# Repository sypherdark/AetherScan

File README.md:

# AetherScan — Autonomous Indoor 3D Scanning Drone

<p align="center">
  <strong>A drone that flies itself through an unknown indoor space, maps it in real time, and exports a 3D reconstruction.</strong>
</p>

AetherScan is a from-scratch indoor drone **autonomy stack** — 6-DoF physics, SLAM,
frontier + coverage exploration, and semantic 3D reconstruction — built to the point
where it demonstrates **coverage parity flying on its own drifting pose estimate vs.
flying on ground truth**, in simulation. The remaining gaps to real hardware are
identified, measured, and tracked in [ROADMAP.md](ROADMAP.md) and
[REALWORLD_READINESS.md](REALWORLD_READINESS.md).

> **What actually runs:** the `redwood_sim/` Python backend (all physics, sensing,
> mapping, planning) streaming state over a WebSocket to a Next.js + React Three Fiber
> dashboard. **You do not need ROS 2 or Gazebo to run AetherScan.** The
> `aetherscan_ws/` ROS 2 workspace is scaffolding for the eventual hardware-transfer
> target — see [Repository layout](#repository-layout).

---

## How it works

Two independent processes with a single clean data contract between them.

```
┌──────────────────────────── redwood_sim/ (Python) ────────────────────────────┐
│                          ALL computation lives here                            │
│                                                                                │
│   physics.py ──► controls.py ──► navigation.py ──► discovery_map.py            │
│   (RK4 6-DoF      (cascaded      (frontier +        (log-odds occupancy        │
│    @ 500 Hz)       PID)           coverage A*)       grid, 0.2 m)              │
│        │              │               │                   │                    │
│   sensors.py    state_estimation.py   scan_matching.py    exporters.py         │
│   (168-ray       (drifting pose       (Olson 2009         (PLY / GLB / SVG     │
│    LiDAR sim)     estimate)            SLAM correction)     deliverables)       │
│                                                                                │
│                     bridge/server.py  ──►  WebSocket :8765  (20 Hz state)      │
└────────────────────────────────────────────────────────────────────────────────┘
                                      │
                          JSON over WebSocket
                                      │
┌──────────────────────── dashboard/ (Next.js + R3F) ───────────────────────────┐
│                       DISPLAY ONLY — zero physics, zero planning               │
│                                                                                │
│   ScanEnvironment   PointCloudRenderer   DiscoveredMap   PathVisualization     │
│   (loads scene GLB) (streams recon cloud)(occupancy grid)(planned path)        │
│                          MissionControl (start / stop / god-mode)              │
└────────────────────────────────────────────────────────────────────────────────┘
```

**Invariant #0:** the dashboard never computes physics or planning. It is a terminal.
Every number it draws was produced in Python and shipped over the socket.

A single mission loop: the drone starts with an **empty** map (everything unknown).
Each tick it raycasts a 168-ray LiDAR against the scene, folds the hits into a
log-odds occupancy grid, picks the next frontier (using a FUEL-style global tour to
avoid re-walking corridors), plans an obstacle-inflated A* path to it, and flies there
under a cascaded PID controller — while a correlative scan-matcher bounds the drift in
its self-estimated pose. Scanned points accumulate into a voxel-deduplicated cloud you
can export as a colored PLY, a Poisson GLB mesh, and an SVG floor plan.

---

## Quick start (no ROS, no Docker, no GPU)

Requires **Python 3.11+** (Apple Silicon: install via Homebrew — the system 3.9
segfaults on the Open3D BVH build) and **Node 18+**.

### 1. Set up the physics backend
```bash
cd redwood_sim
./setup-macos.sh        # creates .venv (Python 3.11) and installs requirements.txt
#  …or manually:
#  python3.11 -m venv .venv && .venv/bin/pip install -r requirements.txt
```

### 2. Run the two processes

**One-shot convenience script** (starts the bridge headless, then the dashboard):
```bash
./run-aetherscan.sh --dashboard            # from repo root
./run-aetherscan.sh --dashboard --scene room_0    # pick a scene
# → http://localhost:3000
```

**Or run them by hand in two terminals:**
```bash
# Terminal 1 — physics bridge (WebSocket ws://127.0.0.1:8765)
cd redwood_sim
.venv/bin/python -m bridge --scene apartment_1

# Terminal 2 — dashboard
cd dashboard
npm install
npm run dev
# → http://localhost:3000
```

Open `http://localhost:3000`, pick a scene, hit **Start Mission**, and watch the drone
explore. The fuchsia **GOD** button enables ~3× time acceleration.

> **Note on scene meshes:** the dashboard's visual `.glb` meshes and the backend's
> collision meshes are **not** in the repo (they're hundreds of MB, generated from the
> Meta Replica dataset). The physics bridge runs fine without them; the 3D viewport
> will be empty until you generate the assets — see [Scene assets](#scene-assets).

### 3. Run the tests
```bash
cd redwood_sim
.venv/bin/python -m pytest tests -q        # 8 state-estimation regression tests
```

---

## The WebSocket protocol

The bridge speaks JSON over `ws://127.0.0.1:8765`, broadcasting state at 20 Hz.

| Message | Direction | Payload |
|---|---|---|
| `hello` | server→client | `visual_mesh_url`, `scene_bounds` (ROS ENU frame, never pre-transformed) |
| `scene_changed` | server→client | same as `hello`, on scene switch |
| `state` (20 Hz) | server→client | `position`, `quaternion`, `velocity`, `tilt`, `altitude`, `coverage_pct`, `total_points`, `path`, `discovery_map`, `map_points` (new points since last frame), `localization{ mode, pos_drift_m, yaw_drift_deg, slam_corrections, slam_match_score, slam_health }`, `god_mode` |
| `set_scene` | client→server | switch the active scene |
| `set_god_mode` | client→server | toggle 3× time acceleration |
| `export_scan` | client→server | run the PLY/GLB/SVG export pipeline async; replies `export_started` / `export_complete{ urls, files, errors }` |

Reconstruction points are streamed as **deltas** (`map_points` = new-since-last-frame),
and the frontend uploads only new points into a preallocated 500k buffer — it never
rebuilds the cloud. All server sends pass through a single `asyncio.Lock` so a
scene-switch can't race the 20 Hz broadcast and drop the connection.

**Coordinate convention:** everything in Python is **Z-up ROS / ENU** (X=forward,
Y=left, Z=up). The Three.js layer applies `rosToThree(x,y,z) = [x, z, -y]` exactly
once, at the scene group. `scene_bounds` cross the wire in the ROS frame, untouched.

Bridge CLI: `python -m bridge --scene <id> [--host 127.0.0.1] [--port 8765] [--rate 20] [--voxel 0.03] [--dt 0.002]`

---

## What's in the autonomy stack

| Module | What it does | Notable detail |
|---|---|---|
| `core/physics.py` | 6-DoF quadrotor rigid body, **RK4 @ 500 Hz** | ~1.45 kg frame, drag, ground effect, Dryden wind; collision resolved per micro-step to prevent tunneling |
| `core/controls.py` | Cascaded PID: position→velocity→attitude→thrust | Correct ZYX-Euler world→body tilt mapping (a swapped-axis bug previously made it fly perpendicular to its command) |
| `core/sensors.py` | 168-ray LiDAR (7 rings × 24), range/normal noise | Configurable FOV (360° RPLIDAR baseline; 87° = D435 camera-class) |
| `core/discovery_map.py` | Log-odds occupancy grid, 0.2 m | Floor hits are FREE at flight altitude; noisy returns can't flip a cell; compact body model fits 0.8 m doorways |
| `core/navigation.py` | Frontier + coverage exploration, A* path-following | FUEL-style global tour ordering: **+15–56 % coverage per meter** |
| `core/state_estimation.py` | Drifting, noisy pose estimate (the sim-to-real seam) | `config.use_estimated_pose` — off for the clean demo |
| `core/scan_matching.py` | Correlative scan-matcher (Olson 2009) + keyframe SLAM | Bounds drift to **0.04–0.10 m** vs. **0.14→0.33 m** unbounded |
| `core/exporters.py` | PLY (semantic-colored) / GLB (Poisson) / SVG floor plan | Written to `dashboard/public/exports/` |

**Headline result:** with `use_estimated_pose=True`, the drone flies entirely on its
own estimate — discovery map, frontier goals, path-following, and trajectory setpoints
all live in the estimated frame — and reaches **coverage parity with ground-truth
navigation** (apartment_1 35.2 % vs 37.0 %; room_0 89.8 % vs 87.2 %), with *lower* tilt
and *fewer* wall contacts. Full audit: [REALWORLD_READINESS.md](REALWORLD_READINESS.md).

---

## Hardware — the physical drone

The simulation defines a real aircraft, and [`hardware/`](hardware/) designs it to
match — **kept in accordance with the software by a checker** that fails if the CAD
ever drifts from the physics model (`hardware/cad/check_against_software.py`).

- **Airframe** — a 360 mm quad-X (1.45 kg, RPLIDAR A2 + RealSense D435i + Jetson
  Orin Nano + Pixhawk/PX4), modelled parametrically in code with
  [build123d](https://github.com/gumyr/build123d). See
  [hardware/cad/](hardware/cad/).
- **Design reviews** — converged through structured multidisciplinary design
  reviews (aerodynamics, mechanical, electrical, software, systems) to a
  **deployment-ready** sign-off, with the sim's inertia reconciled to the
  buildable airframe and the controller re-validated. See
  [hardware/design/](hardware/design/).
- **Electrical** — the Power & Sensor Distribution Board is **defined in code**
  ([atopile](https://github.com/atopile/atopile)) and laid out / 3D-rendered /
  Gerber-exported with **KiCad**. See [hardware/electrical/](hardware/electrical/).
- **Build plan** — funding-staged H0→H4 roadmap; design complete, parts not yet
  bought. [hardware/ROADMAP_HARDWARE.md](hardware/ROADMAP_HARDWARE.md).

A 2-page **investor brief** built from real captured system output lives in
[presentation/](presentation/).

---

## Scene assets

AetherScan ships with **18 Meta Replica scenes** (`apartment_0–2`, `frl_apartment_0–5`,
`office_0–4`, `room_0–2`). For licensing and size reasons the dataset and generated
meshes are **not** committed. To populate the 3D viewport:

1. Obtain the [Replica dataset](https://github.com/facebookresearch/Replica-Dataset)
   and place/symlink scenes under `redwood_sim/data/replica/<id>/`.
2. Generate dashboard visual meshes and backend collision meshes:
   ```bash
   python3 scripts/convert_replica_to_glb.py          # → dashboard/public/meshes/<id>.glb
   python3 scripts/build_collision_meshes_fast.py     # → <id>_collision.ply (~120k tris)
   ```

The physics bridge runs without these (it falls back to built-in/procedural geometry);
they only affect what the dashboard *renders* and what the backend raycasts against.

---

## Repository layout

```
redwood_sim/          ← THE WORKING SYSTEM (Python: physics, sensing, mapping, planning, SLAM)
  core/               ← physics, controls, sensors, discovery_map, navigation, state_estimation, scan_matching, exporters
  bridge/server.py    ← WebSocket bridge :8765
  simulation/engine.py← fixed-timestep mission loop
  tests/              ← state-estimation regression suite
dashboard/            ← Next.js + React Three Fiber UI (display only)
  src/components/three/  ← scene, point cloud, occupancy, path, drone renderers
  src/lib/            ← WebSocket client, scene registry, ROS↔Three transforms
scripts/              ← Replica → GLB conversion, collision-mesh builder, semantics
hardware/             ← THE PHYSICAL DRONE (design, CAD, electrical) — see below
  design/             ← multidisciplinary design reviews & converged spec
  cad/                ← parametric airframe (build123d) + software-accordance checker
  electrical/pcb/     ← code-defined PCB (atopile) + KiCad layout/render/gerbers
  specs/ · bom/       ← system spec, mass/power/inertia budgets, real-parts BOM
presentation/         ← 2-page investor brief (PDF) built from real system output
aetherscan_ws/        ← ROS 2 (Humble) workspace — HARDWARE-TRANSFER TARGET, not required to run the sim
docker/               ← optional containerized sim + dashboard
```

### About the ROS 2 workspace
`aetherscan_ws/` contains a full ROS 2 package set (`description`, `gazebo`,
`navigation`, `perception`, `slam`, `control`, `mission`, `bringup`). It is the
**intended deployment target** for porting the autonomy stack onto a real airframe
(RViz config, URDF/Xacro drone model, Gazebo worlds, launch files). It is **not** the
path that runs the simulation you see in the dashboard — that's `redwood_sim/`. Treat
the ROS 2 side as scaffolding under active development, not a finished product.

---

## Research grounding

The algorithms are drawn from the literature and measured against it:

- **FUEL** (Zhou et al., RA-L 2021) — global tour ordering of frontier vantages.
- **Olson (2009)** — correlative scan matching for the SLAM correction.
- **Emesent Hovermap** field practice — SLAM-health-aware speed gating.
- **DARPA SubT** (CERBERUS, CoSTAR/NeBula) — uncertainty-aware reactive standoffs
  (wall grazes 140→52 on the cluttered scene).

---

## Honest status — what's *not* done

1. **Global loop closure** — SLAM bounds drift locally but there's no pose-graph; long
   (200 m+) missions still accumulate global error.
2. **Sensor latency / rate decimation** — sensors currently fire in lockstep with the
   control loop; real sensors run async with 20–50 ms latency.
3. **Motor model** — no spin-up time constant, thrust saturation curve, or actuator delay.
4. **Controller hardware tuning** — PID gains tuned against perfect feedback; needs a
   noise + latency injection / hardware-in-the-loop pass.
5. **Camera-only support** — an 87° FOV halves coverage; camera-only hardware needs
   yaw-sweep scanning + short-term obstacle memory.
6. **ROS 2 deployment** — `aetherscan_ws/` is scaffolding, not a validated flight stack.

See [ROADMAP.md](ROADMAP.md) for the phased plan.

---

## License

MIT — see [LICENSE](LICENSE).

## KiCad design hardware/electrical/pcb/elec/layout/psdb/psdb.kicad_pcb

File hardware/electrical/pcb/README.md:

# PSDB — code-defined PCB (atopile)

The Power & Sensor Distribution Board, authored **as code** with
[atopile](https://github.com/atopile/atopile) — the same workflow as the airframe
CAD: parametric source → a build → a verifiable artifact, all version-controlled
in-repo. No clicking around a schematic editor.

## Why this tool (chosen 2026-06-23)

We searched for a PCB tool that matches the project's code-first, verifiable
workflow (the way `cad/frame.py` builds the airframe). Two complementary pieces:

| Tool | Role | Analogue in our CAD flow |
|---|---|---|
| **atopile** (`ato`) | **Authors** the board in `.ato` code; compiler solves constraints, **picks real parts (LCSC)**, runs checks, emits a KiCad `.kicad_pcb` + BOM + power-tree | `build123d` / `frame.py` |
| **KiCad** (ERC/DRC/DFM) | **Reviews** the result: DFM, EMC pre-compliance, SPICE testbenches, BOM sourcing (DigiKey/Mouser/LCSC), JLCPCB/PCBWay export | `check_against_software.py` + `render_preview.py` |

atopile runs zero-setup via `uvx --from atopile ato …`.

## The loop (same as the CAD loop)

```bash
# author:   edit elec/src/psdb.ato   (the schematic, as code)
make pcb            # ato build → real parts picked, checks run, KiCad PCB emitted
make pcb-bom        # show the picked-parts BOM (real LCSC #s)
# review:  run the KiCad ERC/DRC + DFM checks
#          on build/builds/psdb/  → DFM / EMC / SPICE findings
```

Build output (`build/`, gitignored) includes `psdb.kicad_pcb`, `psdb.bom.csv`
(real manufacturer + LCSC part numbers), and `power_tree.md`.

## What `psdb.ato` currently builds

The structural power board from [../psdb-design.md](../psdb-design.md): VBAT input
with bulk decoupling, **two isolated 5 V rails** (8 A Jetson / 3 A avionics) each
modelled as its regulator network (input/output caps + inductor + output ferrite
bead), and the battery-sense divider. The compiler picks real passives (Murata,
UNI-ROYAL, …) with LCSC numbers and the build passes atopile's electrical checks.

## Layout, 3D render & fab (KiCad)

KiCad 10 is installed (`/Applications/KiCad.app`), giving `kicad-cli` for renders /
DRC / Gerbers and the GUI for routing.

```bash
make pcb                       # 1. ato build  -> psdb.kicad_pcb (parts + nets)
python3 place_board.py         # 2. clean 2-channel placement + 50x42 mm outline
./fab.sh all                   # 3. KiCad: 3D render + DRC + JLCPCB gerbers -> fab/
```

`fab.sh` produces (in `fab/`, gitignored — regenerate any time):
- `psdb_3d.png`, `psdb_top.png` — photoreal KiCad renders of the real board.
- `drc.json` — design-rule check.
- `gerbers/` + `psdb_gerbers.zip` — fab output.

### Current status — full KiCad project, routed
The PSDB is a **complete KiCad project** in `elec/layout/psdb/`:
`psdb.kicad_pro` + `psdb.kicad_sch` (schematic) + `psdb.kicad_pcb` (routed board).
- **Schematic** — 27 components: the real switching ICs (TI TPS568230 8 A,
  LMR33630 3 A) with full application circuits (5 V feedback dividers, bootstrap,
  VCC decoupling, enable) + INA226 + 2 mΩ shunt for I²C battery telemetry.
- **PCB — fully routed**: 314 copper tracks, 0 unconnected nets, a bottom-layer
  ground pour. DRC clean except cosmetic silkscreen-overlap warnings. Gerbers +
  drill export to `fab/` (`make pcb-fab`).
- Schematic and PCB are **in accordance** by construction — the schematic's net
  labels are generated from the board's netlist.

**Rebuild from scratch:** `make pcb` (place) → `./route.sh` (autoroute via
Freerouting) → `python3 build_schematic.py` (schematic). *Warning:* `make pcb`
wipes `elec/layout/`, discarding routing — only run it to start over.

### Next iterations (same loop)
- Add the switching-controller ICs (TI **TPS568230** 8 A, **LMR33630** 3 A) +
  **INA226** + 2 mΩ shunt, and the connectors / reverse-polarity P-FET + TVS.
  *(The current board is the power-path skeleton: bulk cap, two buck channels of
  passives, sense divider.)*
  **Note:** `ato create part --search` needs an **interactive terminal** (it
  drives a TTY picker — it errors when piped). Run it yourself in a real shell to
  fetch each IC from JLCPCB, or hand-author the component `.ato` + footprint.
- Route copper + a ground pour; clear the silkscreen overlaps.
- Run KiCad review `emc` + `kicad` DFM review; iterate to clean.
- Export the assembled board as STEP so it drops into the CAD assembly.

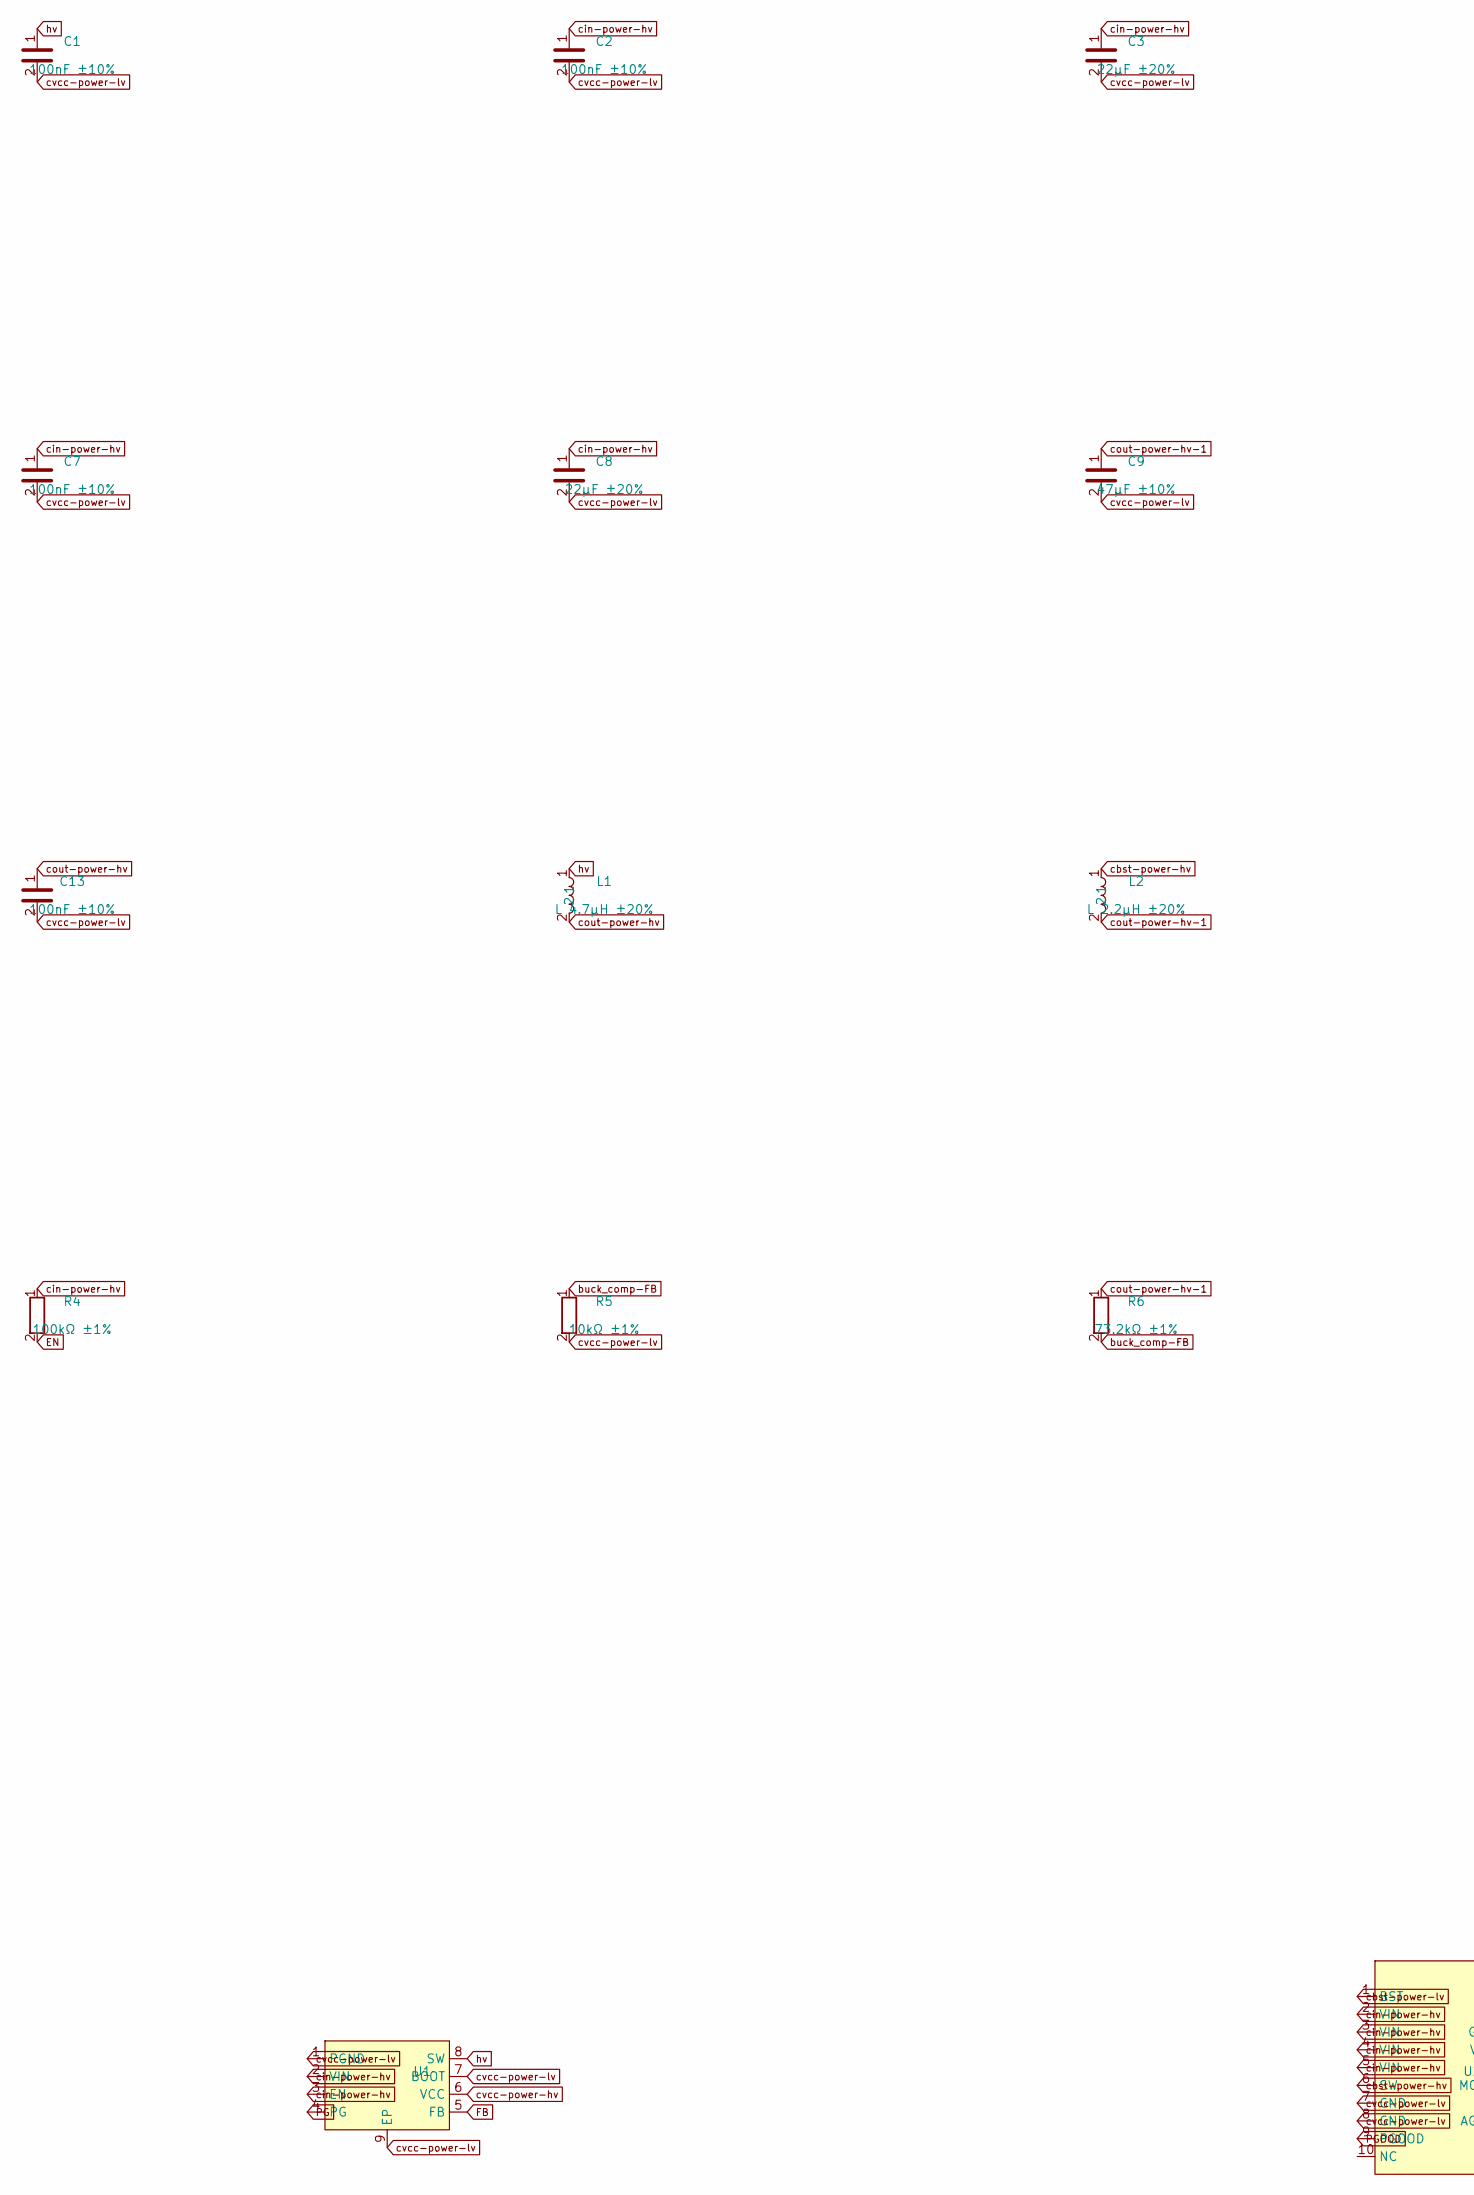
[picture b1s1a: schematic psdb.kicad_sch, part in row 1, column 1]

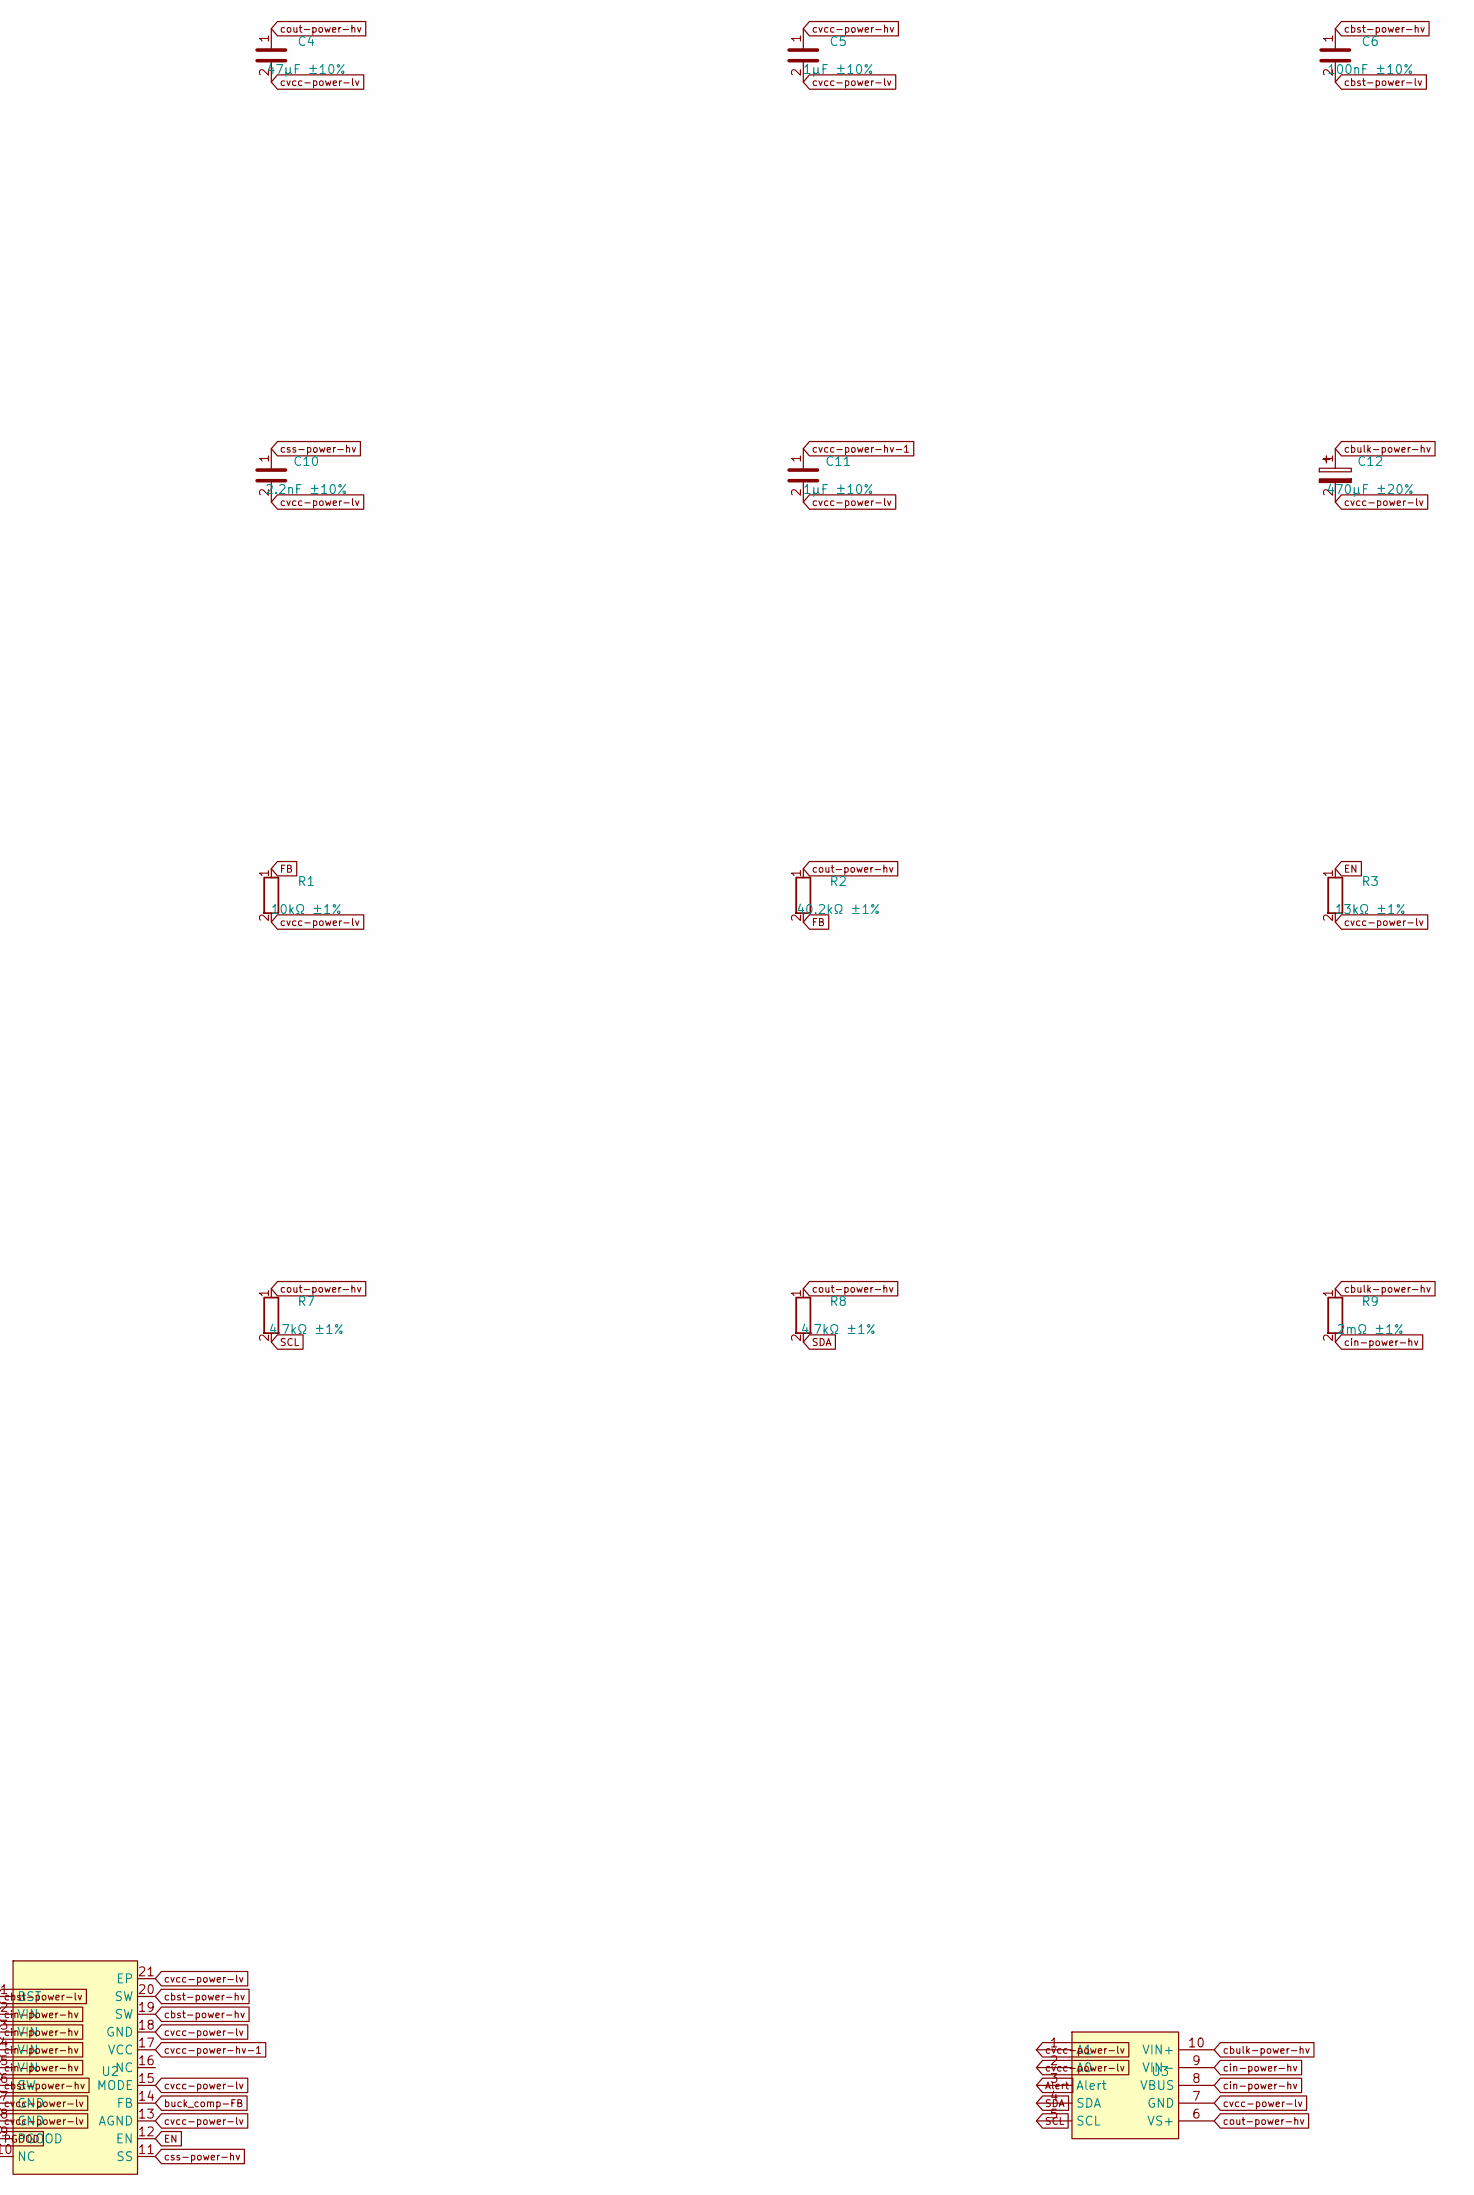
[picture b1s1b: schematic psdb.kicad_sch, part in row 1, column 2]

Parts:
C1, C2, C6, C7, C13: 100nF ±10%
C3, C8: 22µF ±20%
C4, C9: 47µF ±10%
C5, C11: 1µF ±10%
C10: 2.2nF ±10%
C12: 470µF ±20%
L1: L 4.7µH ±20%
L2: L 2.2µH ±20%
R1, R5: 10kΩ ±1%
R2: 40.2kΩ ±1%
R3: 13kΩ ±1%
R4: 100kΩ ±1%
R6: 73.2kΩ ±1%
R7, R8: 4.7kΩ ±1%
R9: 2mΩ ±1%
U1, U2, U3: (no value)

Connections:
Alert: U3.3 (Alert)
EN: R3.1, R4.2, U2.12 (EN)
FB: R1.1, R2.2, U1.5 (FB)
PG: U1.4 (PG)
PGOOD: U2.9 (PGOOD)
SCL: R7.2, U3.5 (SCL)
SDA: R8.2, U3.4 (SDA)
buck_comp-FB: R5.1, R6.2, U2.14 (FB)
cbst-power-hv: C6.1, L2.1, U2.6 (SW), U2.19 (SW), U2.20 (SW)
cbst-power-lv: C6.2, U2.1 (BST)
cbulk-power-hv: C12.1, R9.1, U3.10 (VIN+)
cin-power-hv: C2.1, C3.1, C7.1, C8.1, R4.1, R9.2, U1.2 (VIN), U1.3 (EN), U2.2 (VIN), U2.3 (VIN), U2.4 (VIN), U2.5 (VIN), U3.8 (VBUS), U3.9 (VIN-)
cout-power-hv: C4.1, C13.1, L1.2, R2.1, R7.1, R8.1, U3.6 (VS+)
cout-power-hv-1: C9.1, L2.2, R6.1
css-power-hv: C10.1, U2.11 (SS)
cvcc-power-hv: C5.1, U1.6 (VCC)
cvcc-power-hv-1: C11.1, U2.17 (VCC)
cvcc-power-lv: C1.2, C2.2, C3.2, C4.2, C5.2, C7.2, C8.2, C9.2, C10.2, C11.2, C12.2, C13.2, R1.2, R3.2, R5.2, U1.1 (PGND), U1.7 (BOOT), U1.9 (EP), U2.7 (GND), U2.8 (GND), U2.13 (AGND), U2.15 (MODE), U2.18 (GND), U2.21 (EP), U3.1 (A1), U3.2 (A0), U3.7 (GND)
hv: C1.1, L1.1, U1.8 (SW)

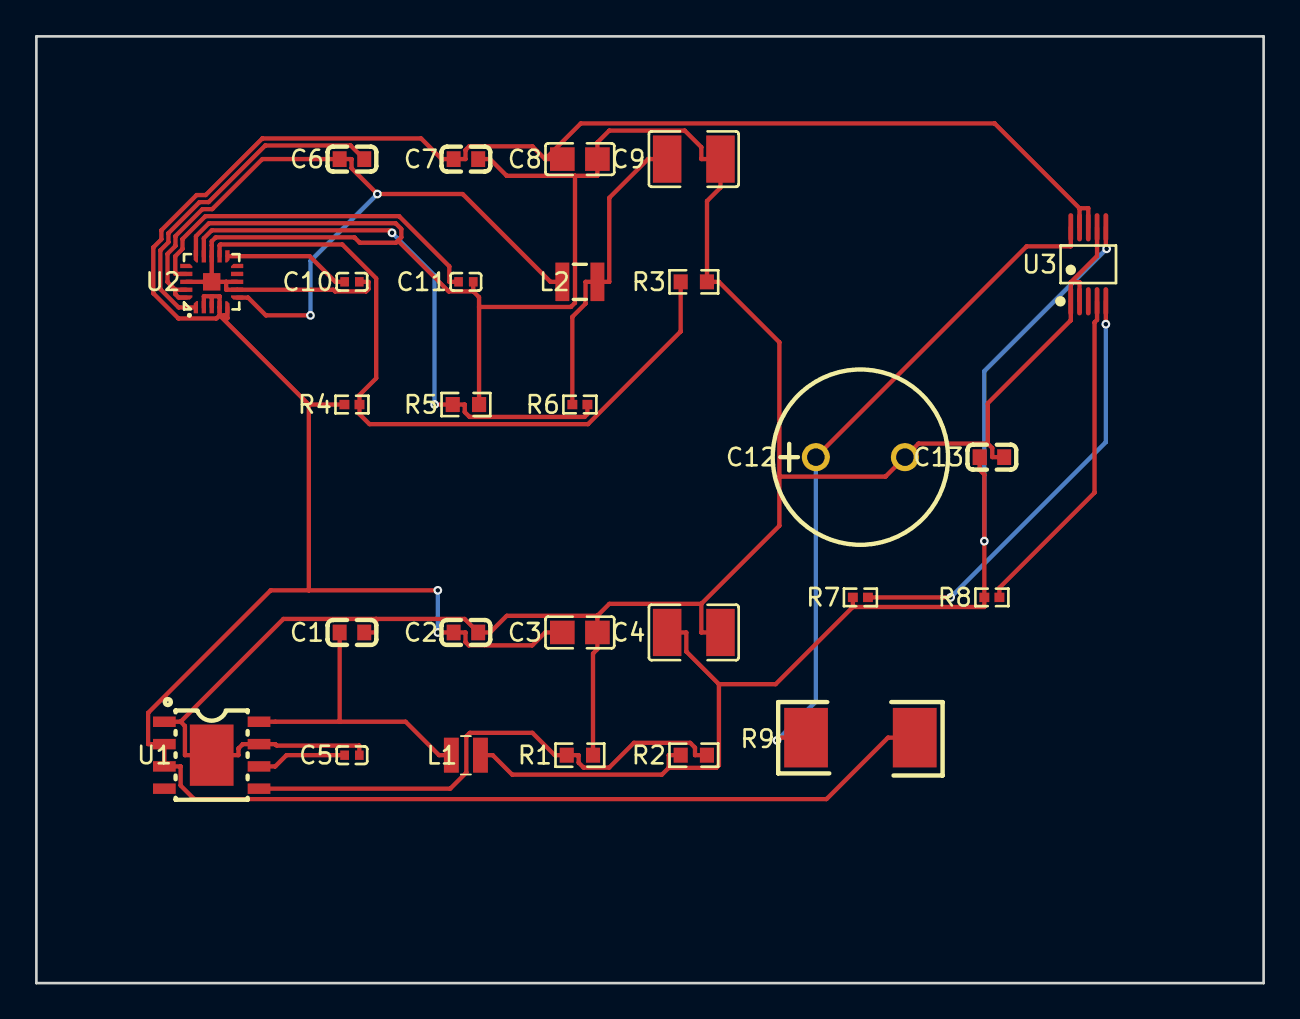
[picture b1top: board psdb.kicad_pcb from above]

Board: 2 copper layers, 70.0 x 54.0 mm, 27 parts (0 on the bottom side), 16 nets.

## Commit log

2026-06-20 Initial commit — AetherScan autonomous indoor 3D scanning drone
    Full autonomy stack: RK4 quadrotor physics (500 Hz), cascaded PID
    controller, 168-ray LiDAR simulation, log-odds occupancy mapping,
    FUEL-style frontier+coverage exploration, correlative SLAM scan-matching
    (Olson 2009), and voxel-deduplicated 3D reconstruction.
    Navigation closes on estimated pose with coverage parity vs ground truth
    (apt_1 35.2% vs 37.0%, room_0 89.8% vs 87.2%). Bridge streams physics
2026-06-20 Tighten .gitignore — exclude all binary assets, drop stray .ply.bak
    Ignore entire data dir and mesh output dirs plus *.ply/*.glb/*.npy/*.zip/*.bak
    globs so no generated assets can leak into the repo. Untrack the one binary
    (apartment.ply.bak) that slipped into the initial commit.
2026-06-20 Rewrite README to match the system that actually runs
    The old README described ROS 2 + Gazebo + RTAB-Map as the system and gave
    `ros2 launch` quick-start commands — but that stack does not run the
    simulation. The working system is the redwood_sim Python backend streaming
    to the Next.js dashboard over WebSocket :8765.
    - Lead with the real two-process architecture (redwood_sim ↔ dashboard)
    - Real quick-start: ./run-aetherscan.sh --dashboard, or the two-terminal
2026-06-23 Add hardware design — airframe CAD, BOM, specs, electrical, roadmap
    Phase H0 (paper drone): a complete digital hardware design that stays in
    accordance with the flight software by construction.
    - cad/parameters.py — single source of truth for every dimension; values that
    originate in redwood_sim (mass, arm length, inertia, tilt, body radius) are
    cited to their source line.
    - cad/check_against_software.py — parses physics.py/config.py and asserts the
2026-06-23 Add sensor brackets, compute tray, full assembly + inertia check
    - cad/sensor_mounts.py — D435 nose L-bracket (look axis +X, FOV clear) and
    belly flow/ToF mount (clear nadir cone).
    - cad/compute_tray.py — Jetson tray (airflow standoffs) + soft-mounted FC pad
    (vibration isolation protects the estimator).
    - cad/assembly.py — places every real component at its mount with datasheet
    mass; computes CG + inertia tensor; compares to physics.py targets. Builds a
2026-06-23 Redesign airframe: streamlined canopy, prop guards, LiDAR mast, nose pod
    The previous airframe was a crude plate-stack. Replaced it with a real indoor
    scanning drone converged through a five-discipline design review.
    with disagreements + resolutions recorded. design/design-spec.md is the converged
    spec. Key resolved decisions:
    - Symmetric quad-X (sim accordance: Ixx=Iyy, identical arms) over deadcat.
    - Top tapered-frustum LiDAR mast, scan plane ~135 mm clear above the prop disc,
2026-06-23 Refine airframe design and freeze the v1 configuration
    grounding (provided key), so they researched competitors (Skydio/DJI/Flyability/
    Matterport/NavVis) and argued from their own knowledge; raw outputs kept outside
    the repo, this is the synthesis + an independent quantitative analysis.
    Vote: P1 focus-the-product (6-0 PASS), P2 inertia-reconcile-first (6-0 PASS),
    P3 guards+5200mAh (0-1-5 no mandate -> trade study), P4 folding-arms-now
    (6-0 PASS), P6 360 top-mast (6-0 PASS).
2026-06-23 Reconcile sim inertia to the buildable airframe + re-validate controller
    0.014/0.014/0.026 → 0.0075/0.0095/0.011 (the CAD-measured values from
    hardware/cad/assembly.py); the old Izz=0.026 was physically unreachable for a
    360 mm quad. parameters.py mirrors the values so the hardware↔software contract
    check stays green.
    Controller gains RETAINED unchanged: on lower inertia at fixed gains the attitude
    loop is faster AND better damped (zeta = kd/2*sqrt(kp*I) rises). A naive
2026-06-23 Finalize hardware design (deployment-ready) and complete electrical design
    convergence. Each round executed actual changes before voting.
    Round 3: ratified the inertia reconciliation (6-0) + construction-progress
    objective + airframe freeze; ELEC was the lone NO on deployment-ready because the
    PSDB/EMI/thermal/telemetry were requirements, not a design.
    Round 4: closed the electrical design ->
    - electrical/psdb-design.md: component-level, schematic-ready PSDB (TI TPS568230
2026-06-23 Adopt atopile for code-defined PCB; build the PSDB from code
    Searched for a PCB tool matching the project's code-first/verifiable workflow
    (like build123d for CAD). Chose:
    - atopile (`ato`) — authors the board in .ato code; the compiler solves
    constraints, picks REAL parts (LCSC), runs electrical checks, and emits a KiCad
    PCB + BOM + power-tree. Runs zero-setup via uvx.
    electrical/pcb/ is a working atopile project: psdb.ato builds the structural PSDB
2026-06-23 Add 2-page investor brief (PDF) from verified live system output
    Verified the live system first (the past "scanning a different structure" bug):
    launched the bridge on apartment_1 + the dashboard, ran an autonomous mission,
    and confirmed the reconstruction is the SAME structure the drone flies in — the
    bridge keys collision + visual mesh on one scene_id, and both resolve to
    apartment_1. Captured real dashboard screenshots at 87.8% coverage / 353K points
    / 58.8 m2.
2026-06-24 Add 3D model of the PSDB from real component STEP models
    build_board_3d.py assembles the actual STEP 3D models atopile fetched (470µF
    electrolytic, 22µF/47µF MLCCs, 2.2µH/1µH inductors) on a representative 52x46mm
    board with XT60 + breakout headers, exporting per-material STL groups.
    render_board_3d.py produces a coloured dark render (presentation/assets/
    psdb_board_3d.png). A combined colored psdb_board.glb is generated for rotfating
    in any 3D viewer (gitignored, regenerable).
2026-06-24 Add PSDB placement + KiCad fab workflow
    place_board.py: positions the 11 footprints into a clean two-buck-channel layout
    and adds a 50x42 mm Edge.Cuts outline by editing the atopile-generated
    psdb.kicad_pcb (atopile preserves manual placement across rebuilds).
    fab.sh: drives KiCad's kicad-cli for the real outputs — 3D render, DRC, and
    JLCPCB Gerbers+drill (zipped). Run after `ato build` + place_board.py.
    Layout/render/fab now use KiCad's real engine; installing KiCad provides
2026-06-24 Install KiCad; render the real PSDB in 3D + export Gerbers
    KiCad 10.0.4 installed (/Applications/KiCad.app). Ran the layout->fab path:
    place_board.py positions the 11 footprints + adds a 50x42 mm outline, then
    fab.sh drives kicad-cli to produce photoreal 3D renders (psdb_kicad_3d.png,
    psdb_kicad_top.png in presentation/assets), DRC, and JLCPCB Gerbers (31 files).
    DRC: no electrical errors — only cosmetic silkscreen overlaps + 15 unconnected
    nets (the board is placed + outlined + rendered but NOT routed yet; routing is
2026-06-24 README: surface the full project (hardware, PCB, investor brief)
    The root README only described the software/sim. Added a Hardware section and
    repo-layout entries pointing to the airframe CAD (build123d + accordance
    code-defined PCB (atopile + KiCad), the build roadmap, and the investor brief —
    so the repo's front door tells the complete story.
    Also noted honestly in the PCB README that `ato create part --search` needs an
    interactive terminal (errors when piped), so fetching the regulator ICs is a
2026-06-24 Harden PCB layout workflow (fix stale-edit board breakage)
    atopile PRESERVES manual layout edits across `ato build`, so re-running
    place_board.py stacked duplicate outlines and an earlier bad edit (a gr_circle
    with `(fill none)`, invalid in KiCad 9+ format) persisted and made the board
    unloadable by kicad-cli. Fix:
    - `make pcb` now wipes elec/layout, rebuilds from atopile, and re-places — a
    clean layout every time.
2026-06-24 PSDB: wire in the real regulator ICs + INA226 (complete schematic)
    The board was a passives-only power-path skeleton; now it has its active silicon
    and full application circuits:
    - Buck8A: TI TPS568230 (8 A) -> 5 V Jetson rail. EN divider (VBAT > EN abs-max),
    bootstrap + VCC + soft-start caps, feedback 73.2k/10k for 5.00 V (Vref 0.6).
    - Buck3A: TI LMR33630 (3 A) -> 5 V avionics rail. EN tied to VIN, bootstrap/VCC,
    feedback 40.2k/10k for 5.02 V (Vref 1.0).
2026-06-25 Add internal project documentation
    A ~4,800-word Word document teaching every part of the project for the pitch:
    the 60-second pitch, problem/market, the full autonomy stack (sense→map→explore
    →SLAM→fly→reconstruct) each explained plain-English then deep, what's proven (the
    real numbers), the aircraft + custom PCB, the engineering rigor story (design
    competition + moat, a full glossary, and a 14-question investor Q&A with strong
    honest answers. Built with docx-js (build_guide.js), validates clean, embeds the
2026-06-25 Clean up repository for publication
    Remove local working and scratch files from version control (kept on disk) and
    tidy documentation references to standard tooling. Core project — simulation,
    hardware design, CAD, electrical, and specs — is unchanged and builds green.
2026-06-25 PSDB: full KiCad project — routed PCB + schematic, all connected
    Completed the electronics into a full KiCad project (elec/layout/psdb/):
    - psdb.kicad_pcb: FULLY ROUTED — 314 copper tracks, 0 unconnected nets, a
    bottom-layer ground pour. Autorouted via Freerouting (pcbnew Specctra DSN
    export -> Freerouting -> SES import), tight cluster placement, fine-pitch rules
    (0.15mm clearance / 0.2mm min drill, JLCPCB-capable). DRC clean except cosmetic
    silkscreen overlaps. Gerbers + drill export.
